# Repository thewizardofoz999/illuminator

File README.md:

# Illuminator

Completely open-source LED board for FRC visual processing tasks.

Idea based on: Sneaky Snakes' Gloworm LEDboard: https://github.com/KahramanAkyuz/Gloworm and
               Gloworm Vision's Gloworm: https://github.com/gloworm-vision/gloworm

Index:

• "Illuminator" is the first version of the design.

• "Illuminator BOOST" is an upgrade board for ILL.v1.

• "Illuminator" is the second version. This version has a MCU (ATmega328) and temperature sensors on both side of the board. Thus it can work with a closed feedback loop algorithm. We'we written an Arduino IDE library for the v2 board. Library files are also included in the repository in software folder.

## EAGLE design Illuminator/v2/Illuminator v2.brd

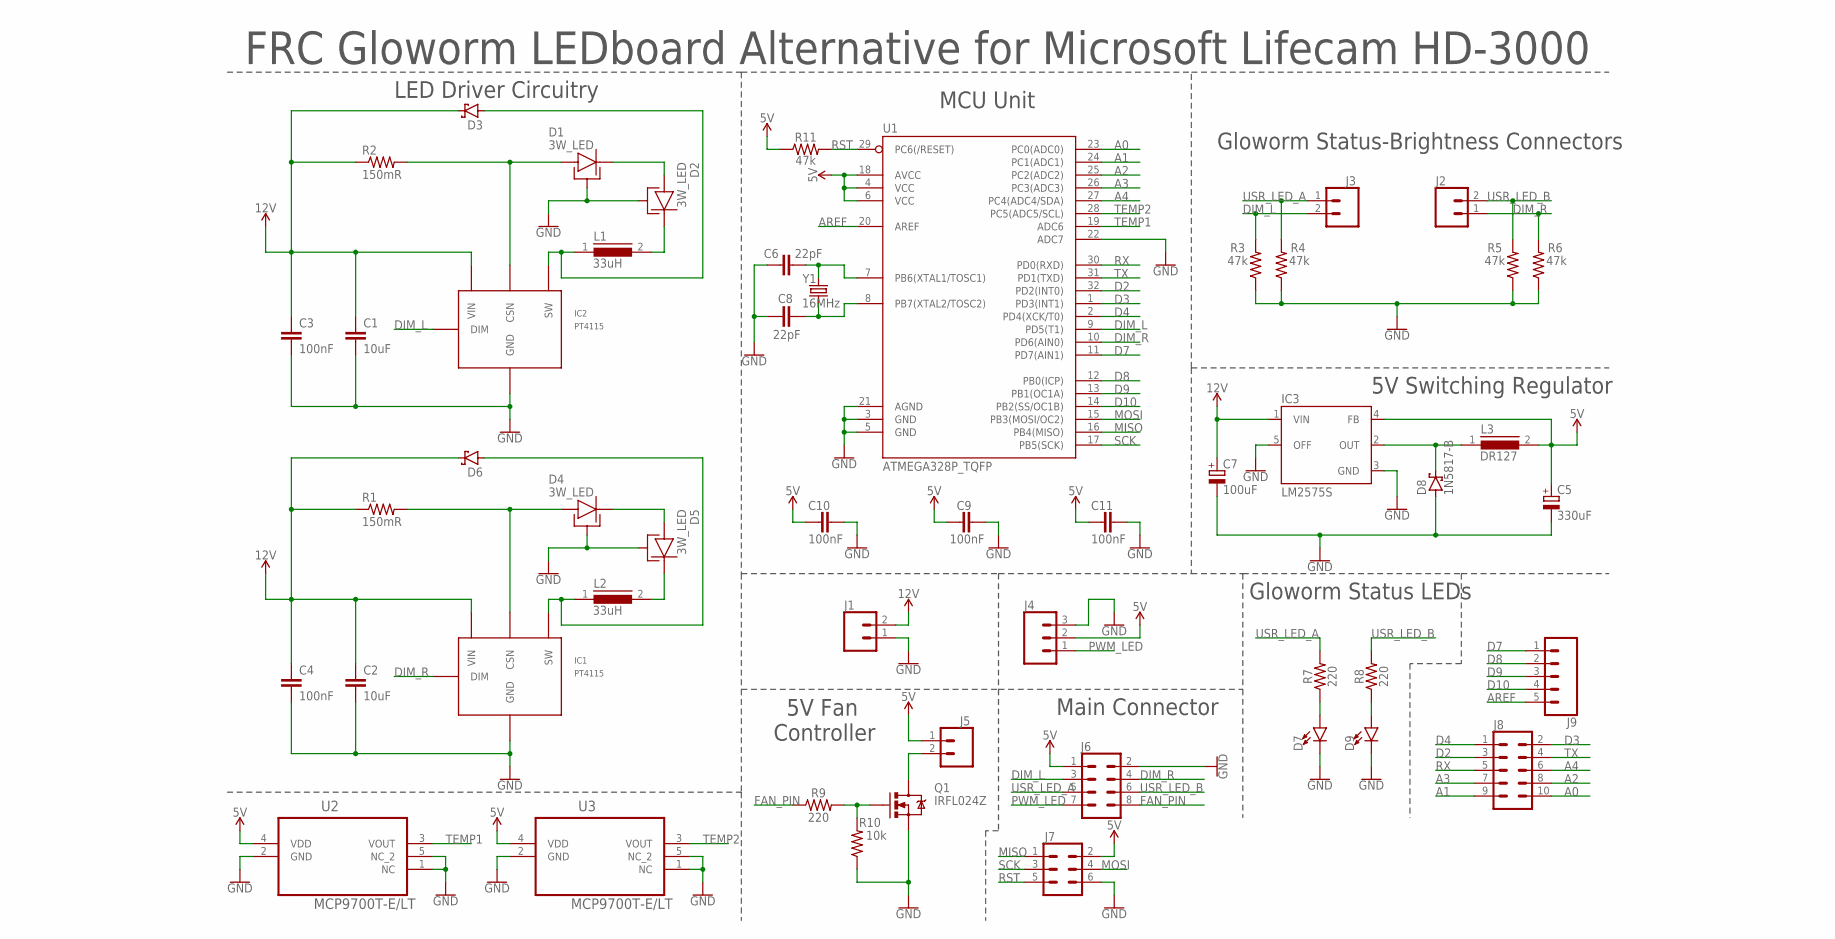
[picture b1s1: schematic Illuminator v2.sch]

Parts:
C1, C2: 10uF; 1206
C3, C4, C9, C10, C11: 100nF; 0805
C5: 330uF; CAPAE1030X1050N
C6, C8: 22pF; 0603
C7: 100uF; CAPAE830X1050N
D1, D2, D4, D5: 3W_LED
D3, D6: SCHOTTKY-DIODESMD; SMB
D7, D9: LED1206; LED-1206
D8: 1N5817-B; DO41-7.6
IC1, IC2: PT4115
IC3: LM2575S; TO263-5
J1: CONN_02SPRING-2.54-RA; SPRINGTERMINAL-2.54MM-2
J2, J3, J5: CONN_02; 1X02
J4: CONN_03; 1X03
J6: CONN_04X2; 2X4
J7: CONN_03X2NO_SILK; 2X3-NS
J8: CONN_05X2NO_SILK; 2X5_NOSILK
J9: CONN_05NO_SILK; 1X05_NO_SILK
L1, L2: 33uH; DR125
L3: DR127
Q1: IRFL024Z; SOT-223
R1, R2: 150mR; R2512
R3, R4, R5, R6, R11: 47k; 0805
R7, R8, R9: 220; 1206
R10: 10k; 1206
U1: ATMEGA328P_TQFP; TQFP32-08
U2, U3: MCP9700T-E/LT; SOT65P210X110-5N
Y1: 16MHz; CRYSTAL-SMD-5X3.2-4PAD

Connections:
5V: C5.1 (+), C9.1, C10.1, C11.1, IC3.4 (FB), J4.2, J5.1, J6.1, J7.2, L3.2, R11.1, U1.4 (VCC), U1.6 (VCC), U1.18 (AVCC), U2.4 (VDD), U3.4 (VDD)
12V: C1.1, C2.1, C3.1, C4.1, C7.1 (+), D3.C, D6.C, IC1.5 (VIN), IC2.5 (VIN), IC3.1 (VIN), J1.2, R1.1, R2.1
A0: J8.10, U1.23 (PC0(ADC0))
A1: J8.9, U1.24 (PC1(ADC1))
A2: J8.8, U1.25 (PC2(ADC2))
A3: J8.7, U1.26 (PC3(ADC3))
A4: J8.6, U1.27 (PC4(ADC4/SDA))
AREF: J9.5, U1.20 (AREF)
D2: J8.3, U1.32 (PD2(INT0))
D3: J8.2, U1.1 (PD3(INT1))
D4: J8.1, U1.2 (PD4(XCK/T0))
D7: J9.1, U1.11 (PD7(AIN1))
D8: J9.2, U1.12 (PB0(ICP))
D9: J9.3, U1.13 (PB1(OC1A))
D10: J9.4, U1.14 (PB2(SS/OC1B))
DIM_L: IC2.3 (DIM), J3.2, J6.3, R3.2, U1.9 (PD5(T1))
DIM_R: IC1.3 (DIM), J2.1, J6.4, R6.2, U1.10 (PD6(AIN0))
FAN_PIN: J6.8, R9.1
GND: C1.2, C2.2, C3.2, C4.2, C5.2 (-), C6.1, C7.2 (-), C8.1, C9.2, C10.2, C11.2, D1.B_PAD, D2.B_PAD, D4.B_PAD, D5.B_PAD, D7.C, D8.A, D9.C, IC1.2 (GND), IC1.2A (GND), IC2.2 (GND), IC2.2A (GND), IC3.3 (GND), IC3.5 (OFF), J1.1, J4.3, J6.2, J7.6, Q1.3 (S), R3.1, R4.1, R5.1, R6.1, R10.1, U1.3 (GND), U1.5 (GND), U1.21 (AGND), U1.22 (ADC7), U2.1 (NC), U2.2 (GND), U2.5 (NC_2), U3.1 (NC), U3.2 (GND), U3.5 (NC_2)
MISO: J7.1, U1.16 (PB4(MISO))
MOSI: J7.4, U1.15 (PB3(MOSI/OC2))
unnamed: D4.ANODE, IC1.4 (CSN), R1.2
unnamed: D1.ANODE, IC2.4 (CSN), R2.2
unnamed: D1.CATHODE, D2.ANODE
unnamed: D3.A, IC2.1 (SW), L1.1
unnamed: D2.CATHODE, L1.2
unnamed: D4.CATHODE, D5.ANODE
unnamed: D6.A, IC1.1 (SW), L2.1
unnamed: D5.CATHODE, L2.2
unnamed: C8.2, U1.8 (PB7(XTAL2/TOSC2)), Y1.1
unnamed: D8.C, IC3.2 (OUT), L3.1
unnamed: D7.A, R7.1
unnamed: D9.A, R8.1
unnamed: Q1.1 (G), R9.2, R10.2
unnamed: J5.2, Q1.2 (D), Q1.4 (D)
unnamed: C6.2, U1.7 (PB6(XTAL1/TOSC1)), Y1.3 (2)
PWM_LED: J4.1, J6.7
RST: J7.5, R11.2, U1.29 (PC6(/RESET))
RX: J8.5, U1.30 (PD0(RXD))
SCK: J7.3, U1.17 (PB5(SCK))
TEMP1: U1.19 (ADC6), U2.3 (VOUT)
TEMP2: U1.28 (PC5(ADC5/SCL)), U3.3 (VOUT)
TX: J8.4, U1.31 (PD1(TXD))
USR_LED_A: J3.1, J6.5, R4.2, R7.2
USR_LED_B: J2.2, J6.6, R5.2, R8.2

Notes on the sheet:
FRC Gloworm LEDboard Alternative for Microsoft Lifecam HD-3000
LED Driver Circuitry
5V Switching Regulator
5V Fan Controller
Gloworm Status-Brightness Connectors
Gloworm Status LEDs
Main Connector
MCU Unit

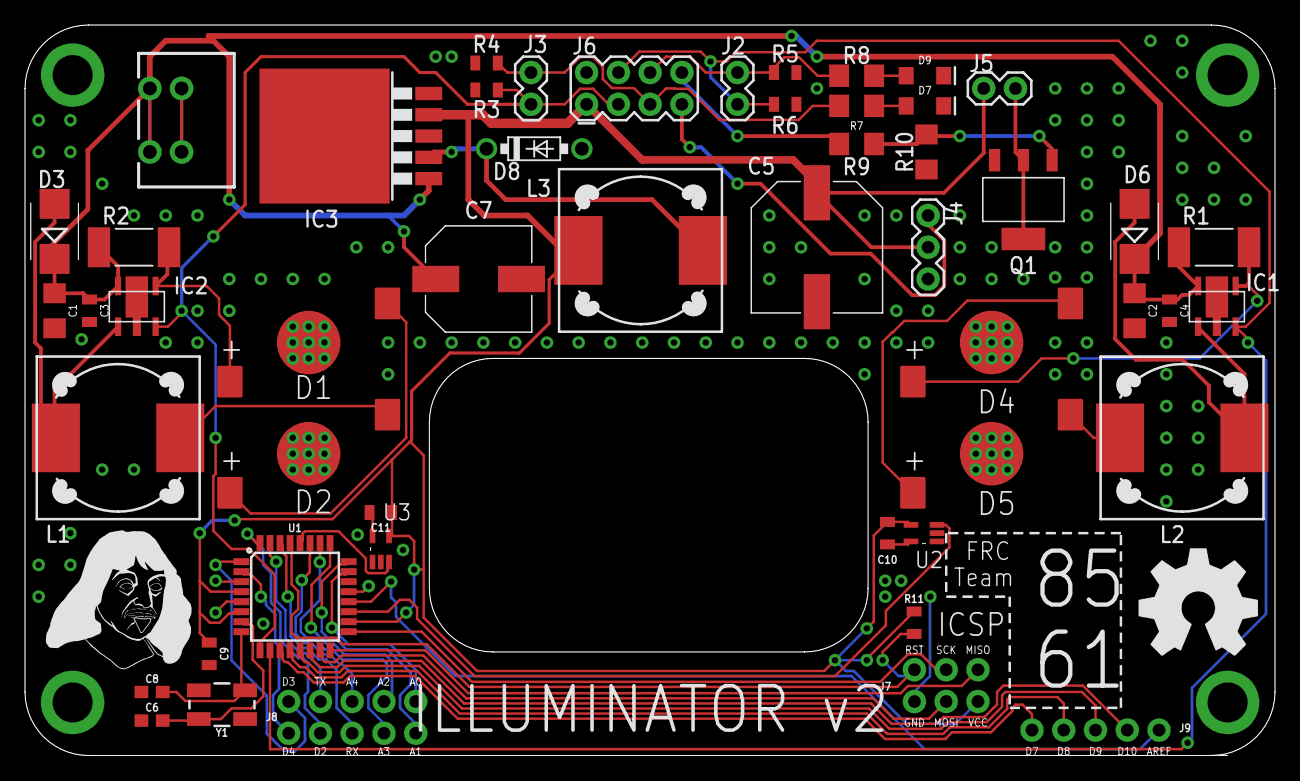
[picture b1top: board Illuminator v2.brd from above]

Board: 2 copper layers, 99.9 x 58.4 mm, 51 parts (0 on the bottom side), 45 nets.

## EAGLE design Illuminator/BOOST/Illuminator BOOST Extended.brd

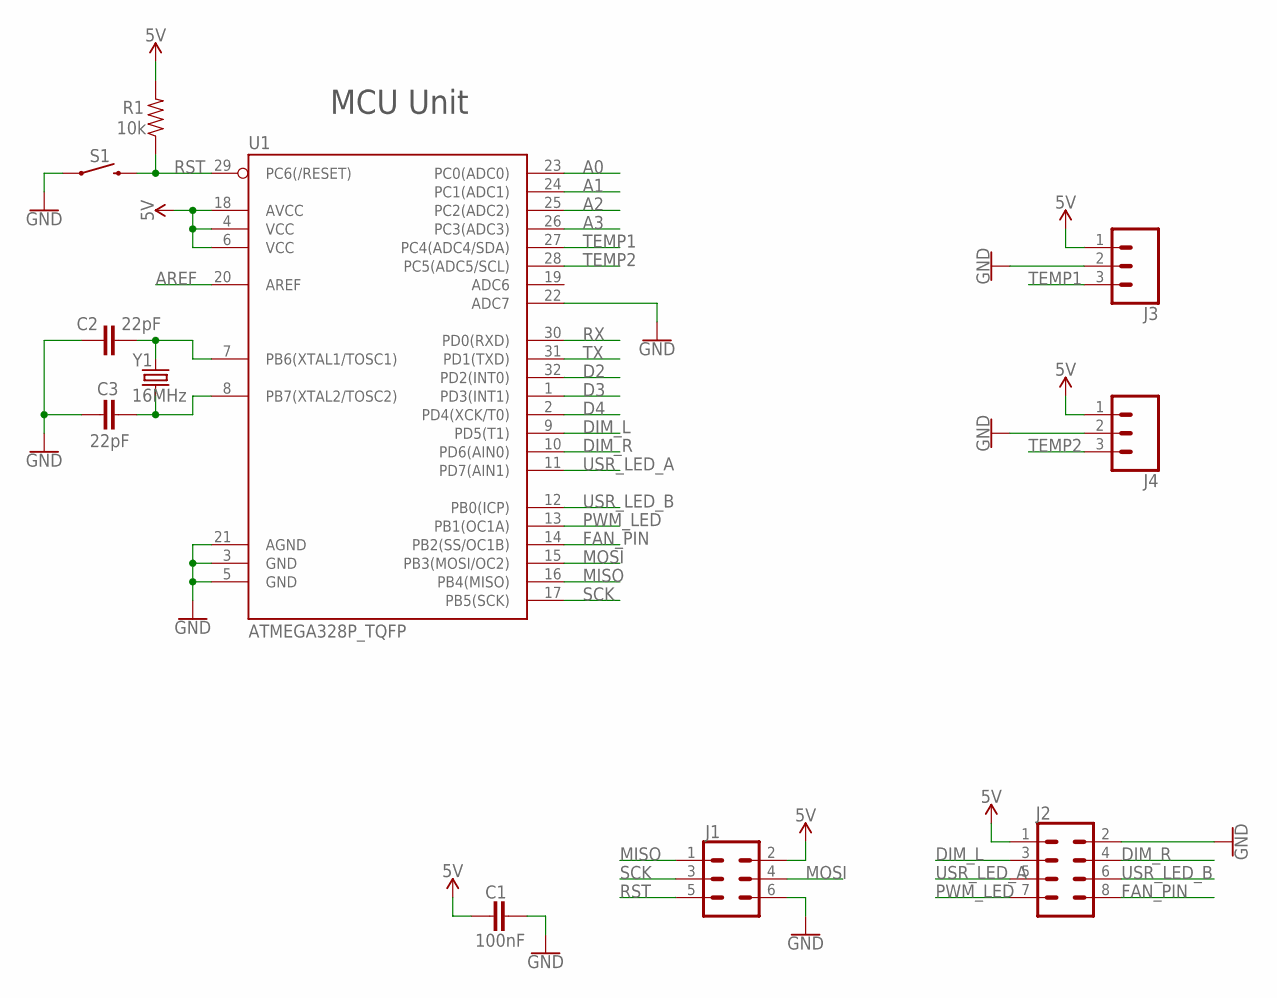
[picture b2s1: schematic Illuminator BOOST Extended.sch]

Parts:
C1: 100nF; 0805
C2, C3: 22pF; 0603
J1: CONN_03X2NO_SILK; 2X3-NS
J2: CONN_04X2; 2X4
J3, J4: CONN_03JST-PTH-VERT; JST-3-PTH-VERT
R1: 10k; 1206
S1: MOMENTARY-SWITCH-SPST-SMD-6.0X3.5MM; TACTILE_SWITCH_SMD_6.0X3.5MM
U1: ATMEGA328P_TQFP; TQFP32-08
Y1: 16MHz; CRYSTAL-SMD-5X3.2-4PAD

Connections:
5V: C1.1, J1.2, J2.1, J3.1, J4.1, R1.2, U1.4 (VCC), U1.6 (VCC), U1.18 (AVCC)
A0: U1.23 (PC0(ADC0))
A1: U1.24 (PC1(ADC1))
A2: U1.25 (PC2(ADC2))
A3: U1.26 (PC3(ADC3))
AREF: U1.20 (AREF)
D2: U1.32 (PD2(INT0))
D3: U1.1 (PD3(INT1))
D4: U1.2 (PD4(XCK/T0))
DIM_L: J2.3, U1.9 (PD5(T1))
DIM_R: J2.4, U1.10 (PD6(AIN0))
FAN_PIN: J2.8, U1.14 (PB2(SS/OC1B))
GND: C1.2, C2.1, C3.1, J1.6, J2.2, J3.2, J4.2, S1.1, U1.3 (GND), U1.5 (GND), U1.21 (AGND), U1.22 (ADC7)
MISO: J1.1, U1.16 (PB4(MISO))
MOSI: J1.4, U1.15 (PB3(MOSI/OC2))
unnamed: C3.2, U1.8 (PB7(XTAL2/TOSC2)), Y1.1
unnamed: C2.2, U1.7 (PB6(XTAL1/TOSC1)), Y1.3 (2)
PWM_LED: J2.7, U1.13 (PB1(OC1A))
RST: J1.5, R1.1, S1.2, U1.29 (PC6(/RESET))
RX: U1.30 (PD0(RXD))
SCK: J1.3, U1.17 (PB5(SCK))
TEMP1: J3.3, U1.27 (PC4(ADC4/SDA))
TEMP2: J4.3, U1.28 (PC5(ADC5/SCL))
TX: U1.31 (PD1(TXD))
USR_LED_A: J2.5, U1.11 (PD7(AIN1))
USR_LED_B: J2.6, U1.12 (PB0(ICP))

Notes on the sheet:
MCU Unit

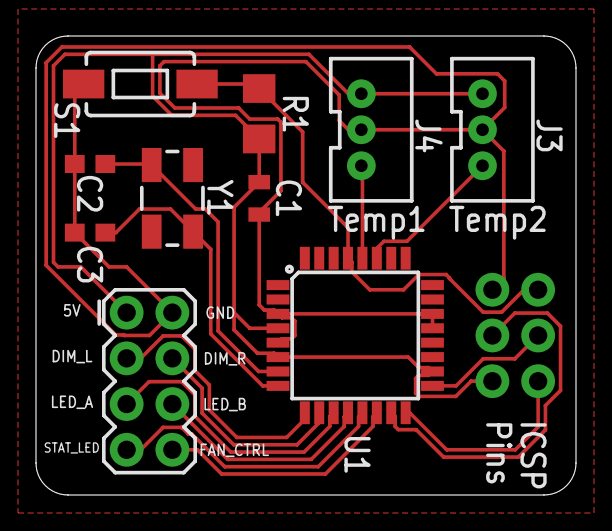
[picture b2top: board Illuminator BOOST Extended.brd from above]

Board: 2 copper layers, 30.0 x 25.5 mm, 11 parts (0 on the bottom side), 16 nets.

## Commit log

2021-08-03 Arduino IDE library for v2 board

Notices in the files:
parts and their libraries:
SparkFun-Connectors: Licensing: Creative Commons ShareAlike 4.0 International - https://creativecommons.org/licenses/by-sa/4.0
